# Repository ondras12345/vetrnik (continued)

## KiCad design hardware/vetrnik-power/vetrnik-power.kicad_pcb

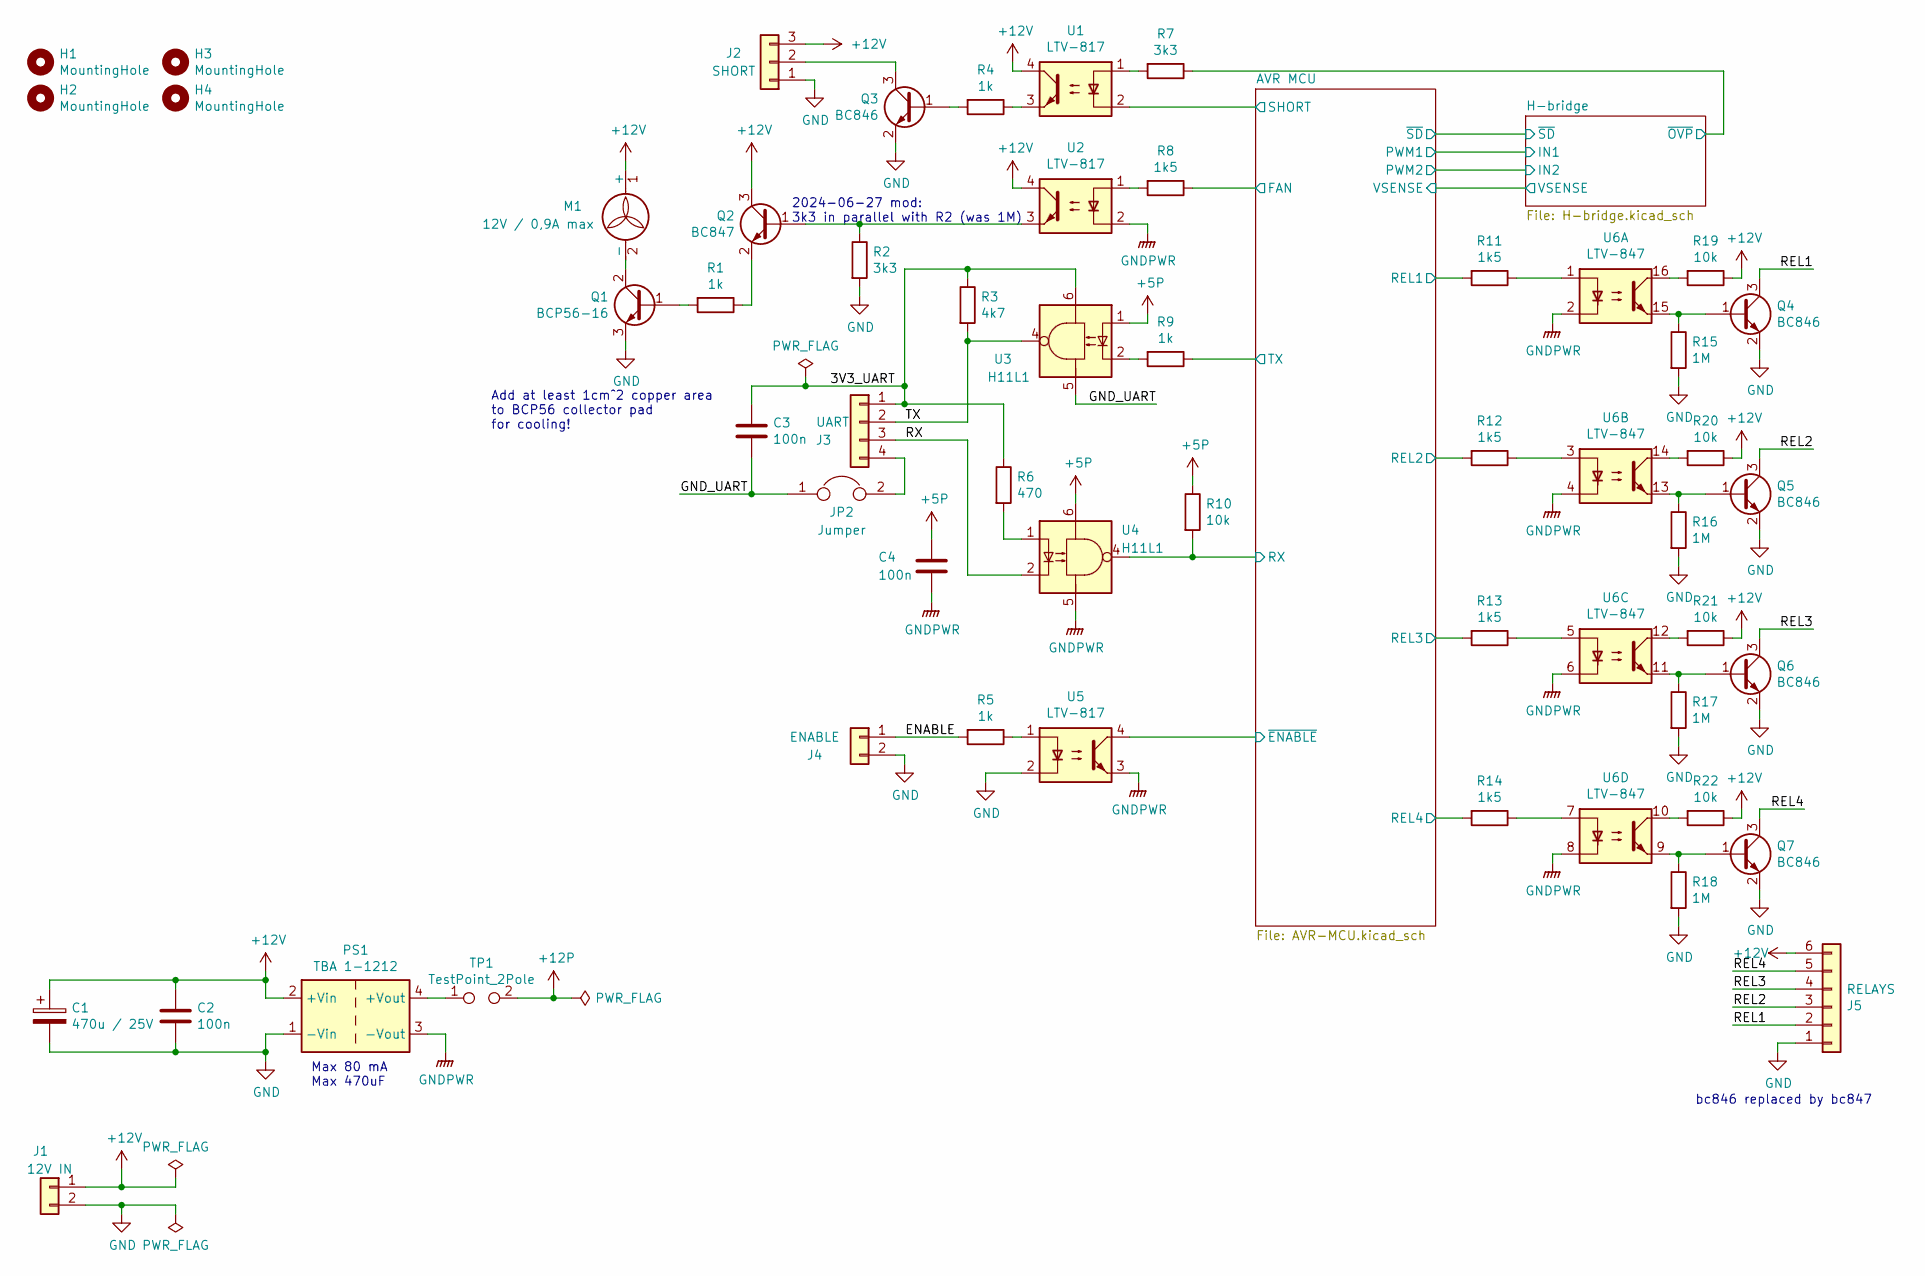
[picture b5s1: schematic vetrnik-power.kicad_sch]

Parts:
C1: 470u / 25V; CP_Radial_D10.0mm_P5.00mm
C2, C3, C4: 100n; C_1206_3216Metric_Pad1.33x1.80mm_HandSolder
H1, H2, H3, H4: MountingHole; MountingHole_3.2mm_M3
J1: 12V IN; Molex_KK-254_AE-6410-02A_1x02_P2.54mm_Vertical
J2: SHORT; Molex_KK-254_AE-6410-03A_1x03_P2.54mm_Vertical
J3: UART; Molex_KK-254_AE-6410-04A_1x04_P2.54mm_Vertical
J4: ENABLE; Molex_KK-254_AE-6410-02A_1x02_P2.54mm_Vertical
J5: RELAYS; Molex_KK-254_AE-6410-06A_1x06_P2.54mm_Vertical
JP2: Jumper; R_1206_3216Metric_Pad1.30x1.75mm_HandSolder
M1: 12V / 0,9A max; Molex_KK-254_AE-6410-02A_1x02_P2.54mm_Vertical
PS1: TBA 1-1212; Converter_DCDC_Murata_MEE1SxxxxSC_THT
Q1: BCP56-16; SOT-223-3_TabPin2
Q2: BC847; SOT-23
Q3, Q4, Q5, Q6, Q7: BC846; SOT-23
R1, R4, R5, R9: 1k; R_1206_3216Metric_Pad1.30x1.75mm_HandSolder
R2, R7: 3k3; R_1206_3216Metric_Pad1.30x1.75mm_HandSolder
R3: 4k7; R_1206_3216Metric_Pad1.30x1.75mm_HandSolder
R6: 470; R_1206_3216Metric_Pad1.30x1.75mm_HandSolder
R8, R11, R12, R13, R14: 1k5; R_1206_3216Metric_Pad1.30x1.75mm_HandSolder
R10, R19, R20, R21, R22: 10k; R_1206_3216Metric_Pad1.30x1.75mm_HandSolder
R15, R16, R17, R18: 1M; R_1206_3216Metric_Pad1.30x1.75mm_HandSolder
TP1: TestPoint_2Pole; PinHeader_1x02_P2.54mm_Vertical
U1, U2, U5: LTV-817; DIP-4_W7.62mm
U3, U4: H11L1; DIP-6_W7.62mm_LongPads
U6: LTV-847; DIP-16_W7.62mm

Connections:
+5P: C4.1, R10.1, U3.1, U4.6; also elsewhere on the board
+12P: TP1.2; also elsewhere on the board
+12V: C1.1, C2.1, J1.1, J2.3, J5.6, M1.1 (+), PS1.2 (+Vin), Q2.3 (C), R19.1, R20.1, R21.1, R22.1, U1.4, U2.4
/3V3_UART: C3.1, J3.1, R3.1, R6.1, U3.6
/AVR MCU/REL1: R11.2; also elsewhere on the board
/AVR MCU/REL2: R12.2; also elsewhere on the board
/AVR MCU/REL3: R13.2; also elsewhere on the board
/AVR MCU/REL4: R14.2; also elsewhere on the board
/AVR MCU/RX: R10.2, U4.4; also elsewhere on the board
/AVR MCU/SHORT: U1.2; also elsewhere on the board
/AVR MCU/TX: R9.1; also elsewhere on the board
/AVR MCU/~ENABLE: U5.4; also elsewhere on the board
/ENABLE: J4.1, R5.2
/GND_UART: C3.2, JP2.1, U3.5
/H-bridge/~OVP: R7.1; also elsewhere on the board
/REL1: J5.2, Q4.3 (C)
/REL2: J5.3, Q5.3 (C)
/REL3: J5.4, Q6.3 (C)
/REL4: J5.5, Q7.3 (C)
/RX: J3.3, U4.2
/TX: J3.2, R3.2, U3.4
GND: C1.2, C2.2, J1.2, J2.1, J4.2, J5.1, PS1.1 (-Vin), Q1.3 (E), Q3.2 (E), Q4.2 (E), Q5.2 (E), Q6.2 (E), Q7.2 (E), R2.2, R15.2, R16.2, R17.2, R18.2, U5.2
unnamed: J2.2, Q3.3 (C)
unnamed: J3.4, JP2.2
unnamed: M1.2 (-), Q1.2 (C), Q1.4 (C)
unnamed: PS1.4 (+Vout), TP1.1
unnamed: Q1.1 (B), R1.2
unnamed: Q2.1 (B), R2.1, U2.3
unnamed: Q2.2 (E), R1.1
unnamed: Q3.1 (B), R4.2
unnamed: Q4.1 (B), R15.1, U6.15
unnamed: Q5.1 (B), R16.1, U6.13
unnamed: Q6.1 (B), R17.1, U6.11
unnamed: Q7.1 (B), R18.1, U6.9
unnamed: R4.1, U1.3
unnamed: R5.1, U5.1
unnamed: R6.2, U4.1
unnamed: R7.2, U1.1
unnamed: R8.2, U2.1
unnamed: R9.2, U3.2
unnamed: R11.1, U6.1
unnamed: R12.1, U6.3
unnamed: R13.1, U6.5
unnamed: R14.1, U6.7
unnamed: R19.2, U6.16
unnamed: R20.2, U6.14
unnamed: R21.2, U6.12
unnamed: R22.2, U6.10

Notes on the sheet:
Add at least 1cm^2 copper area to BCP56 collector pad for cooling!
2024-06-27 mod: 3k3 in parallel with R2 (was 1M)
Max 80 mA Max 470uF
bc846 replaced by bc847

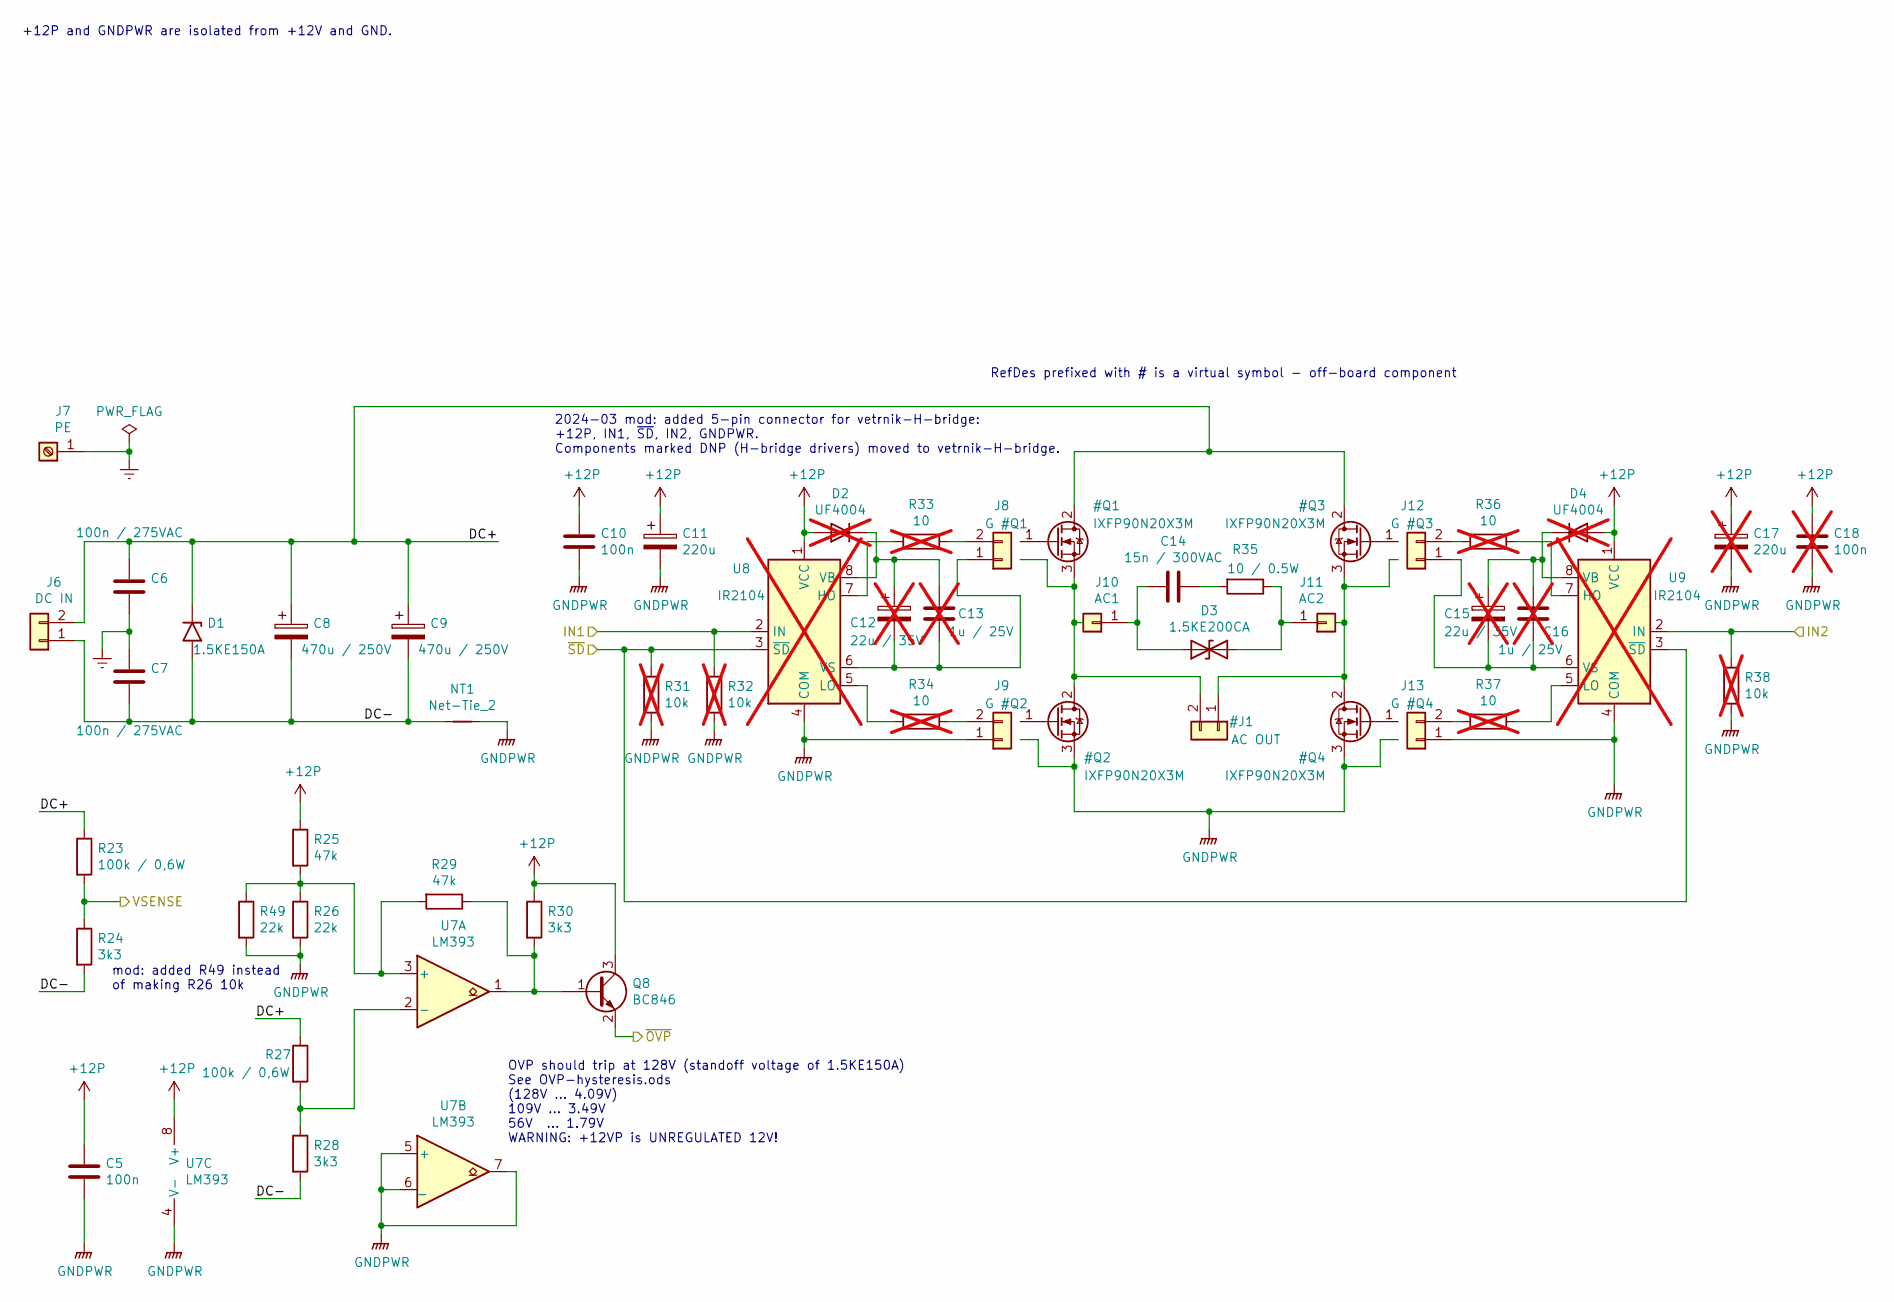
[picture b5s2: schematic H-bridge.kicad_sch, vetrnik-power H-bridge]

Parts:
C5, C10: 100n; C_1206_3216Metric_Pad1.33x1.80mm_HandSolder
C6, C7: 100n / 275VAC; C_Rect_L26.5mm_W10.5mm_P22.50mm_MKS4
C8, C9: 470u / 250V; CP_Radial_D30.0mm_P10.00mm_SnapIn
C11: 220u; CP_Radial_D8.0mm_P3.50mm
C12, C15: 22u / 35V; CP_Radial_D5.0mm_P2.00mm; not fitted
C13, C16: 1u / 25V; C_1206_3216Metric_Pad1.33x1.80mm_HandSolder; not fitted
C14: 15n / 300VAC; C_Rect_L18.0mm_W5.0mm_P15.00mm_FKS3_FKP3
C17: 220u; CP_Radial_D8.0mm_P3.50mm; not fitted
C18: 100n; C_1206_3216Metric_Pad1.33x1.80mm_HandSolder; not fitted
D1: 1.5KE150A; D_DO-201AE_P15.24mm_Horizontal
D2, D4: UF4004; D_DO-41_SOD81_P10.16mm_Horizontal; not fitted
D3: 1.5KE200CA; D_DO-201AE_P15.24mm_Horizontal
J6: DC IN; DG270-10.0-02P-14-00A
J7: PE; FS1536
J8: G #Q1; Molex_KK-254_AE-6410-02A_1x02_P2.54mm_Vertical
J9: G #Q2; Molex_KK-254_AE-6410-02A_1x02_P2.54mm_Vertical
J10: AC1; FS1536
J11: AC2; FS1536
J12: G #Q3; Molex_KK-254_AE-6410-02A_1x02_P2.54mm_Vertical
J13: G #Q4; Molex_KK-254_AE-6410-02A_1x02_P2.54mm_Vertical
NT1: Net-Tie_2; NetTie-2_SMD_Pad2.0mm
Q8: BC846; SOT-23
R23, R27: 100k / 0,6W; R_Axial_DIN0207_L6.3mm_D2.5mm_P10.16mm_Horizontal
R24, R28, R30: 3k3; R_1206_3216Metric_Pad1.30x1.75mm_HandSolder
R25, R29: 47k; R_1206_3216Metric_Pad1.30x1.75mm_HandSolder
R26, R49: 22k; R_1206_3216Metric_Pad1.30x1.75mm_HandSolder
R31, R32, R38: 10k; R_1206_3216Metric_Pad1.30x1.75mm_HandSolder; not fitted
R33, R34, R36, R37: 10; R_1206_3216Metric_Pad1.30x1.75mm_HandSolder; not fitted
R35: 10 / 0.5W; R_Axial_DIN0309_L9.0mm_D3.2mm_P12.70mm_Horizontal
U7: LM393; SOIC-8_3.9x4.9mm_P1.27mm
U8, U9: IR2104; SOIC-8_3.9x4.9mm_P1.27mm; not fitted

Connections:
+12P: C5.1, C10.1, C11.1, C17.1, C18.1, D2.2 (A), D4.2 (A), Q8.3 (C), R25.1, R30.1, U7.8 (V+), U8.1 (VCC), U9.1 (VCC); also elsewhere on the board
/AVR MCU/VSENSE: R23.2, R24.1; also elsewhere on the board
/AVR MCU/~SD: R31.1, U8.3 (~SD), U9.3 (~SD); also elsewhere on the board
/H-bridge/IN1: R32.1, U8.2 (IN); also elsewhere on the board
/H-bridge/IN2: R38.1, U9.2 (IN); also elsewhere on the board
/H-bridge/~OVP: Q8.2 (E); also elsewhere on the board
Earth: C6.2, C7.1, J7.1
unnamed: C12.1, C13.1, D2.1 (K), U8.8 (VB)
unnamed: C12.2, C13.2, J8.1, U8.6 (VS)
unnamed: C14.1, R35.2
unnamed: C14.2, D3.2 (A2), J10.1
unnamed: C15.1, C16.1, D4.1 (K), U9.8 (VB)
unnamed: C15.2, C16.2, J12.1, U9.6 (VS)
unnamed: D3.1 (A1), J11.1, R35.1
unnamed: J8.2, R33.1
unnamed: J9.2, R34.1
unnamed: J12.2, R36.2
unnamed: J13.2, R37.2
unnamed: Q8.1 (B), R29.1, R30.2, U7.1
unnamed: R25.2, R26.1, R29.2, R49.1, U7.3 (+)
unnamed: R27.2, R28.1, U7.2 (-)
unnamed: R33.2, U8.7 (HO)
unnamed: R34.2, U8.5 (LO)
unnamed: R36.1, U9.7 (HO)
unnamed: R37.1, U9.5 (LO)

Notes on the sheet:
2024-03 mod: added 5-pin connector for vetrnik-H-bridge: +12P, IN1, ~{SD}, IN2, GNDPWR. Components marked DNP (H-bridge drivers) moved to vetrnik-H-bridge.
+12P and GNDPWR are isolated from +12V and GND.
RefDes prefixed with # is a virtual symbol - off-board component
OVP should trip at 128V (standoff voltage of 1.5KE150A) See OVP-hysteresis.ods (128V ... 4.09V) 109V ... 3.49V 56V ... 1.79V WARNING: +12VP is UNREGULATED 12V!
mod: added R49 instead of making R26 10k

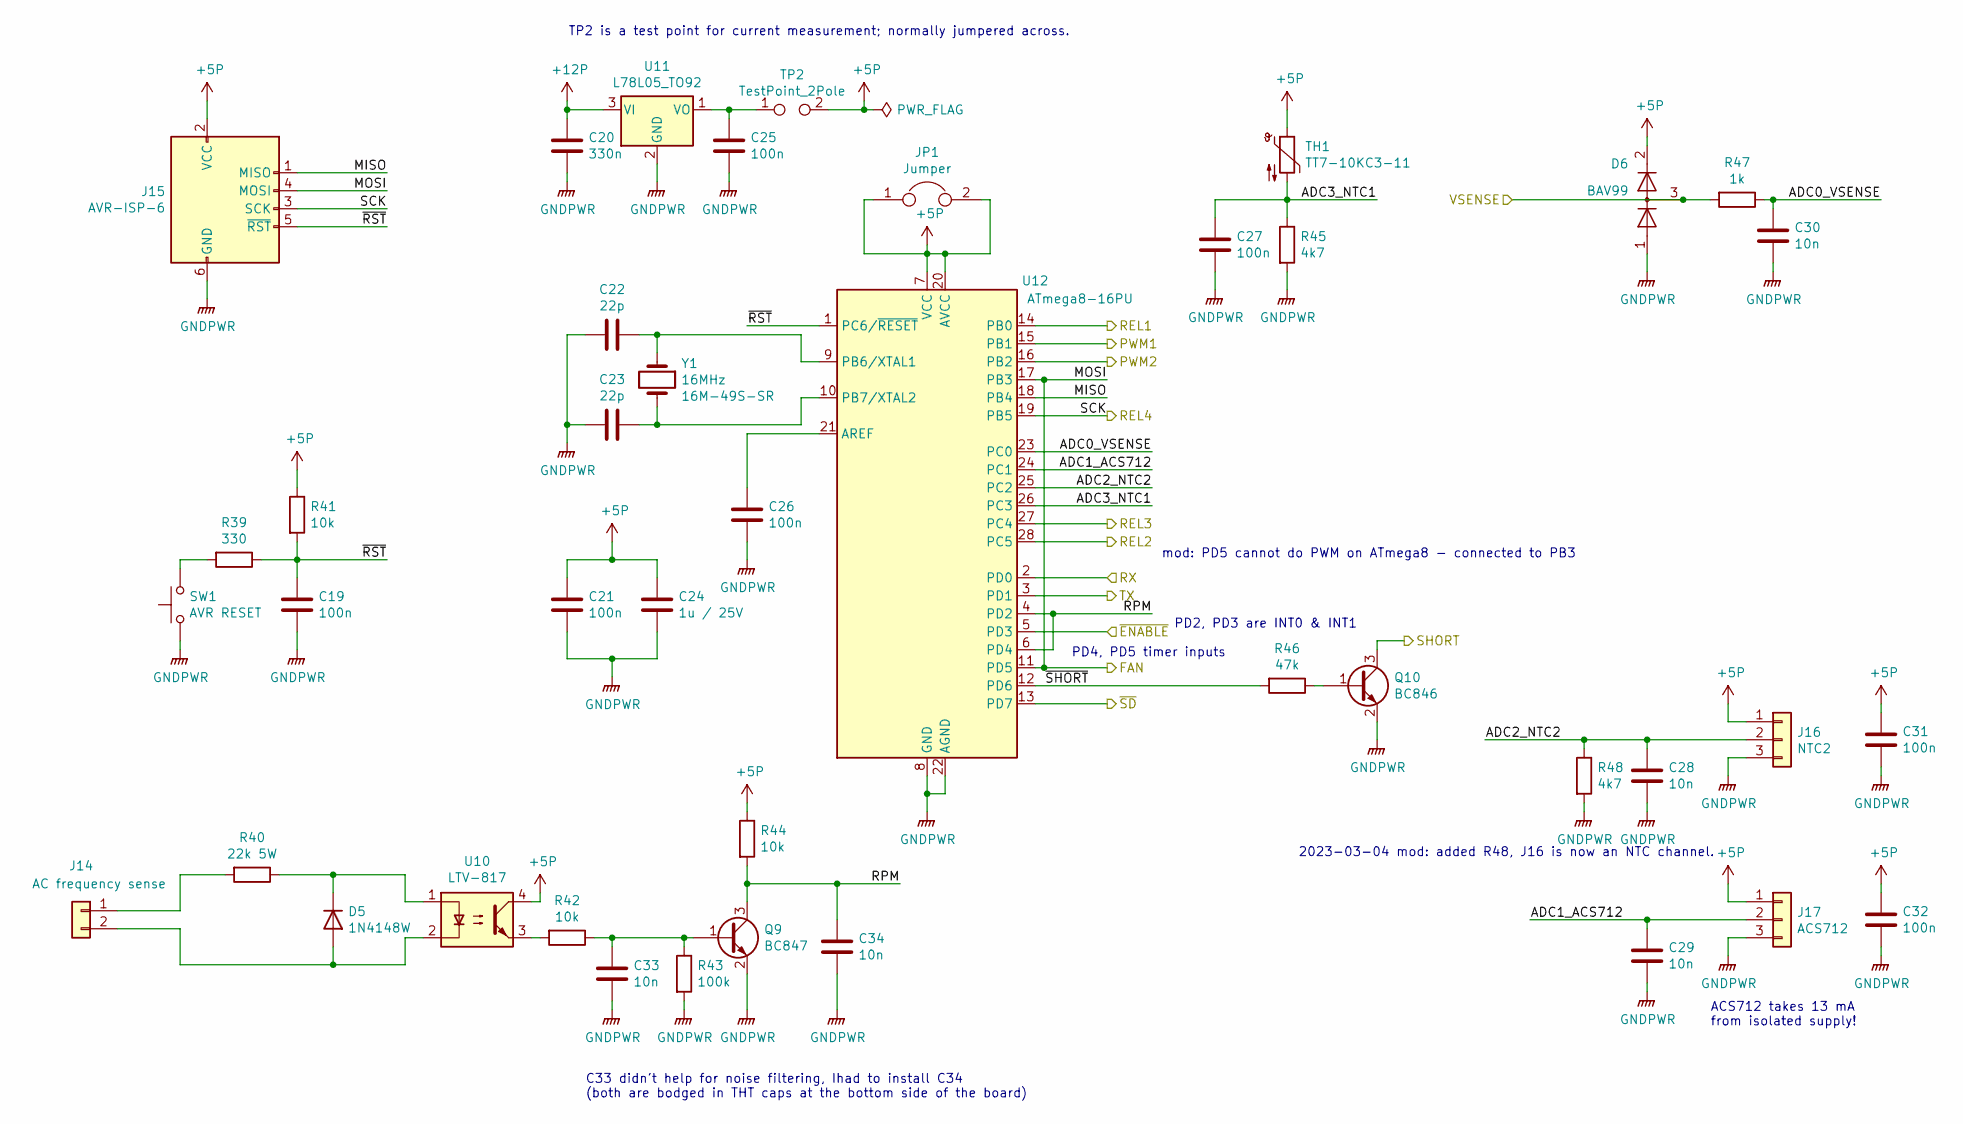
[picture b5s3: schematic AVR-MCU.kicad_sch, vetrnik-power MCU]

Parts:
C19, C21, C25, C26, C27, C31, C32: 100n; C_1206_3216Metric_Pad1.33x1.80mm_HandSolder
C20: 330n; C_1206_3216Metric_Pad1.33x1.80mm_HandSolder
C22, C23: 22p; C_1206_3216Metric_Pad1.33x1.80mm_HandSolder
C24: 1u / 25V; C_1206_3216Metric_Pad1.33x1.80mm_HandSolder
C28, C29, C30, C33, C34: 10n; C_1206_3216Metric_Pad1.33x1.80mm_HandSolder
D5: 1N4148W; D_SOD-123
D6: BAV99; SOT-23
J14: AC frequency sense; Molex_KK-254_AE-6410-02A_1x02_P2.54mm_Vertical
J15: AVR-ISP-6; IDC-Header_2x03_P2.54mm_Vertical
J16: NTC2; Molex_KK-254_AE-6410-03A_1x03_P2.54mm_Vertical
J17: ACS712; Molex_KK-254_AE-6410-03A_1x03_P2.54mm_Vertical
JP1: Jumper; R_1206_3216Metric_Pad1.30x1.75mm_HandSolder
Q9: BC847; SOT-23
Q10: BC846; SOT-23
R39: 330; R_1206_3216Metric_Pad1.30x1.75mm_HandSolder
R40: 22k 5W; R_Axial_DIN0922_L20.0mm_D9.0mm_P30.48mm_Horizontal
R41, R42, R44: 10k; R_1206_3216Metric_Pad1.30x1.75mm_HandSolder
R43: 100k; R_1206_3216Metric_Pad1.30x1.75mm_HandSolder
R45, R48: 4k7; R_1206_3216Metric_Pad1.30x1.75mm_HandSolder
R46: 47k; R_1206_3216Metric_Pad1.30x1.75mm_HandSolder
R47: 1k; R_1206_3216Metric_Pad1.30x1.75mm_HandSolder
SW1: AVR RESET; SW_PUSH_6mm_H4.3mm
TH1: TT7-10KC3-11; Molex_KK-254_AE-6410-02A_1x02_P2.54mm_Vertical
TP2: TestPoint_2Pole; PinHeader_1x02_P2.54mm_Vertical
U10: LTV-817; DIP-4_W7.62mm
U11: L78L05_TO92; TO-92L_HandSolder
U12: ATmega8-16PU; DIP-28_W7.62mm_Socket
Y1: 16MHz; Crystal_HC49-U_Vertical

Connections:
+5P: C21.1, C24.1, C31.1, C32.1, D6.2 (A), J15.2 (VCC), J16.1, J17.1, JP1.1, JP1.2, R41.1, R44.1, TH1.1, TP2.2, U10.4, U12.7 (VCC), U12.20 (AVCC); also elsewhere on the board
+12P: C20.1, U11.3 (VI); also elsewhere on the board
/AVR MCU/ADC0_VSENSE: C30.1, R47.1, U12.23 (PC0)
/AVR MCU/ADC1_ACS712: C29.1, J17.2, U12.24 (PC1)
/AVR MCU/ADC2_ACS712_2: C28.1, J16.2, R48.1, U12.25 (PC2)
/AVR MCU/ADC3_NTC1: C27.1, R45.1, TH1.2, U12.26 (PC3)
/AVR MCU/MISO: J15.1 (MISO), U12.18 (PB4)
/AVR MCU/REL1: U12.14 (PB0); also elsewhere on the board
/AVR MCU/REL2: U12.28 (PC5); also elsewhere on the board
/AVR MCU/REL3: U12.27 (PC4); also elsewhere on the board
/AVR MCU/REL4: J15.3 (SCK), U12.19 (PB5); also elsewhere on the board
/AVR MCU/RPM: C34.1, Q9.3 (C), R44.2, U12.4 (PD2), U12.6 (PD4)
/AVR MCU/RX: U12.2 (PD0); also elsewhere on the board
/AVR MCU/SHORT: Q10.3 (C); also elsewhere on the board
/AVR MCU/TX: U12.3 (PD1); also elsewhere on the board
/AVR MCU/VSENSE: D6.3 (K), R47.2; also elsewhere on the board
/AVR MCU/~ENABLE: U12.5 (PD3); also elsewhere on the board
/AVR MCU/~RST: C19.1, J15.5 (~RST), R39.1, R41.2, U12.1 (PC6/~RESET)
/AVR MCU/~SD: U12.13 (PD7); also elsewhere on the board
/AVR MCU/~SHORT: R46.2, U12.12 (PD6)
/H-bridge/IN1: U12.15 (PB1); also elsewhere on the board
/H-bridge/IN2: U12.16 (PB2); also elsewhere on the board
unnamed: C22.1, U12.9 (PB6/XTAL1), Y1.1
unnamed: C23.1, U12.10 (PB7/XTAL2), Y1.2
unnamed: C25.1, TP2.1, U11.1 (VO)
unnamed: C26.1, U12.21 (AREF)
unnamed: D5.1 (K), R40.1, U10.1
unnamed: D5.2 (A), J14.2, U10.2
unnamed: J14.1, R40.2
unnamed: C33.1, Q9.1 (B), R42.1, R43.1
unnamed: Q10.1 (B), R46.1
unnamed: R39.2, SW1.2
unnamed: R42.2, U10.3

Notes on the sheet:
mod: PD5 cannot do PWM on ATmega8 - connected to PB3
C33 didn't help for noise filtering, Ihad to install C34 (both are bodged in THT caps at the bottom side of the board)
TP2 is a test point for current measurement; normally jumpered across.
PD2, PD3 are INT0 & INT1
PD4, PD5 timer inputs
2023-03-04 mod: added R48, J16 is now an NTC channel.
ACS712 takes 13 mA from isolated supply!

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
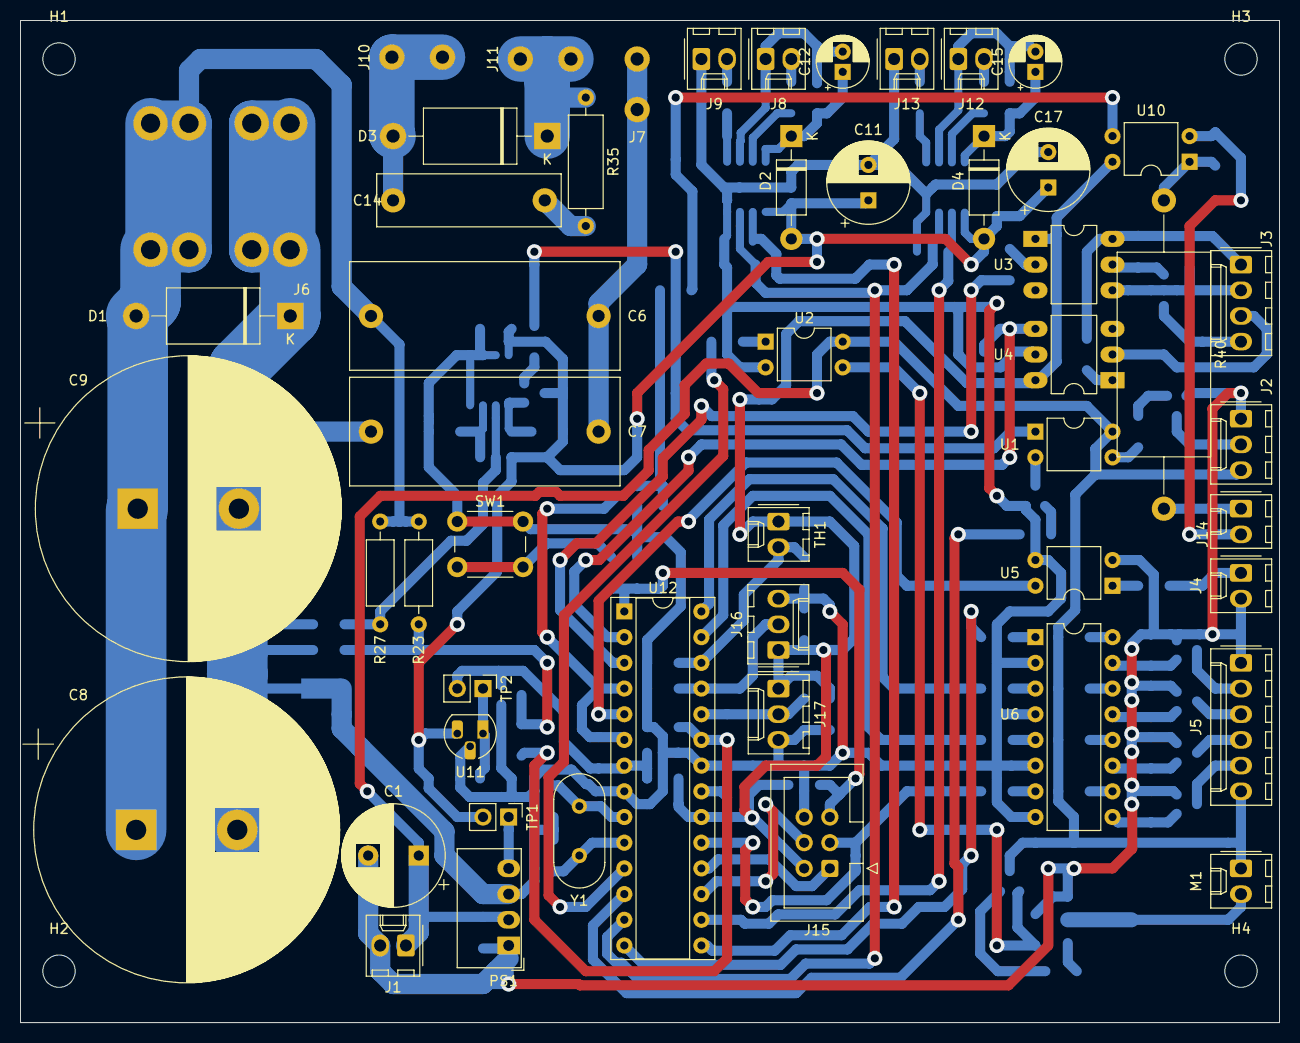
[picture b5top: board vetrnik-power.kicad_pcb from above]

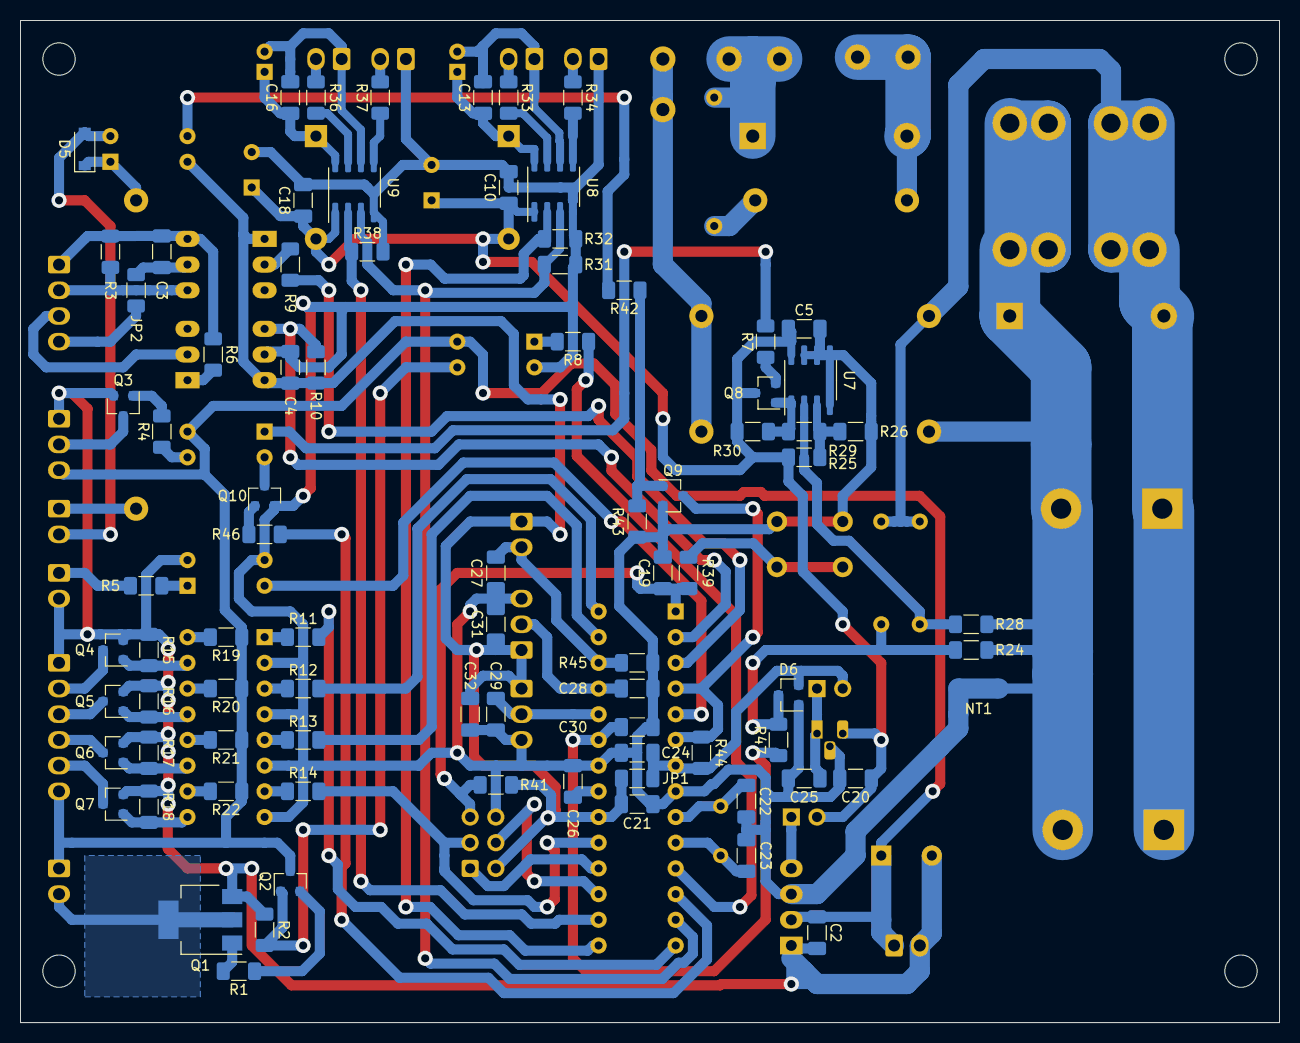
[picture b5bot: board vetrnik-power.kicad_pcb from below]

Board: 2 copper layers, 124.5 x 99.1 mm, 138 parts (83 on the bottom side), 95 nets.

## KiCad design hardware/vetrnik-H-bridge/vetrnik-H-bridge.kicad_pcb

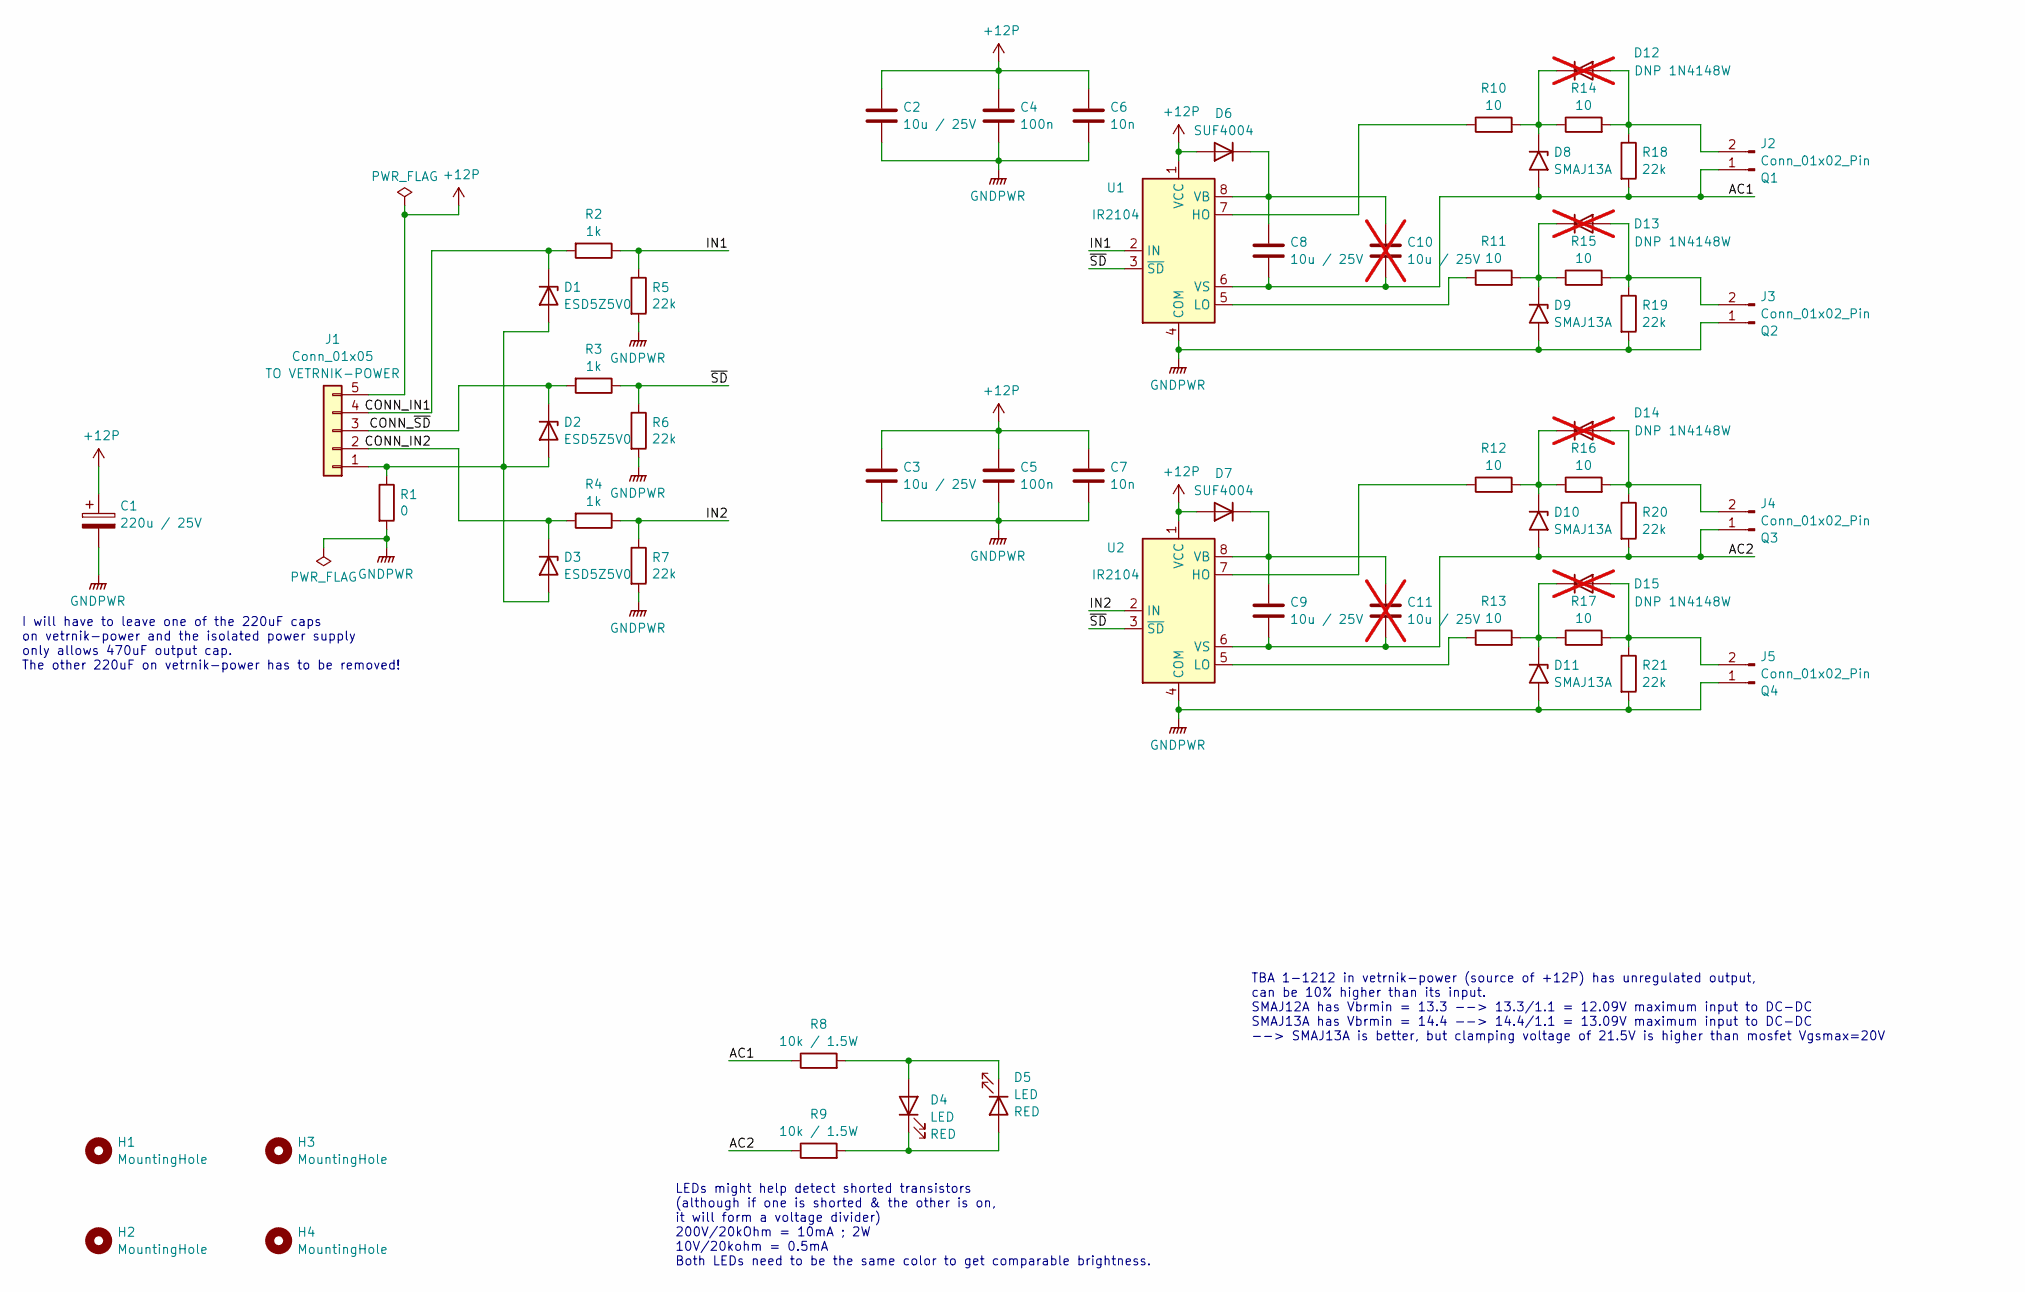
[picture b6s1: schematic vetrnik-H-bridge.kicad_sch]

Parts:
C1: 220u / 25V; CP_Elec_8x10
C2, C3, C8, C9: 10u / 25V; C_1206_3216Metric_Pad1.33x1.80mm_HandSolder
C4, C5: 100n; C_1206_3216Metric_Pad1.33x1.80mm_HandSolder
C6, C7: 10n; C_1206_3216Metric_Pad1.33x1.80mm_HandSolder
C10, C11: 10u / 25V; C_1206_3216Metric_Pad1.33x1.80mm_HandSolder; not fitted
D1, D2, D3: ESD5Z5V0; D_SOD-523
D4, D5: LED; LED_1206_3216Metric_Pad1.42x1.75mm_HandSolder
D6, D7: SUF4004; D_MELF_Handsoldering
D8, D9, D10, D11: SMAJ13A; D_SMA
D12, D13, D14, D15: DNP 1N4148W; D_SOD-123; not fitted
H1, H2, H3, H4: MountingHole; MountingHole_3.2mm_M3
J1: Conn_01x05; SolderWire-0.25sqmm_1x05_P4.2mm_D0.65mm_OD1.7mm_Relief
J2, J3, J4, J5: Conn_01x02_Pin; SolderWire-0.15sqmm_1x02_P4mm_D0.5mm_OD1.5mm_Relief
R1: 0; R_1206_3216Metric_Pad1.30x1.75mm_HandSolder
R2, R3, R4: 1k; R_1206_3216Metric_Pad1.30x1.75mm_HandSolder
R5, R6, R7, R18, R19, R20, R21: 22k; R_1206_3216Metric_Pad1.30x1.75mm_HandSolder
R8, R9: 10k / 1.5W; R_2512_6332Metric_Pad1.40x3.35mm_HandSolder
R10, R11, R12, R13, R14, R15, R16, R17: 10; R_1206_3216Metric_Pad1.30x1.75mm_HandSolder
U1, U2: IR2104; SOIC-8_3.9x4.9mm_P1.27mm

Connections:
+12P: C1.1, C2.1, C3.1, C4.1, C5.1, C6.1, C7.1, D6.2 (A), D7.2 (A), J1.5, U1.1 (VCC), U2.1 (VCC)
/AC1: C8.2, C10.2, D8.2 (A2), J2.1, R8.1, R18.2, U1.6 (VS)
/AC2: C9.2, C11.2, D10.2 (A2), J4.1, R9.1, R20.2, U2.6 (VS)
/CONN_IN1: D1.1 (K), J1.4, R2.2
/CONN_IN2: D3.1 (K), J1.2, R4.2
/CONN_~SD: D2.1 (K), J1.3, R3.2
/IN1: R2.1, R5.1, U1.2 (IN)
/IN2: R4.1, R7.1, U2.2 (IN)
/~SD: R3.1, R6.1, U1.3 (~SD), U2.3 (~SD)
GNDPWR: C1.2, C2.2, C3.2, C4.2, C5.2, C6.2, C7.2, D9.2 (A2), D11.2 (A2), J3.1, J5.1, R1.2, R5.2, R6.2, R7.2, R19.2, R21.2, U1.4 (COM), U2.4 (COM)
unnamed: D1.2 (A), D2.2 (A), D3.2 (A), J1.1, R1.1
unnamed: D4.2 (A), D5.1 (K), R8.2
unnamed: D4.1 (K), D5.2 (A), R9.2
unnamed: C8.1, C10.1, D6.1 (K), U1.8 (VB)
unnamed: C9.1, C11.1, D7.1 (K), U2.8 (VB)
unnamed: D10.1 (A1), D14.1 (K), R12.2, R16.1
unnamed: D11.1 (A1), D15.1 (K), R13.2, R17.1
unnamed: D12.2 (A), J2.2, R14.2, R18.1
unnamed: D8.1 (A1), D12.1 (K), R10.2, R14.1
unnamed: D13.2 (A), J3.2, R15.2, R19.1
unnamed: D9.1 (A1), D13.1 (K), R11.2, R15.1
unnamed: D14.2 (A), J4.2, R16.2, R20.1
unnamed: D15.2 (A), J5.2, R17.2, R21.1
unnamed: R10.1, U1.7 (HO)
unnamed: R11.1, U1.5 (LO)
unnamed: R12.1, U2.7 (HO)
unnamed: R13.1, U2.5 (LO)

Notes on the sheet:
LEDs might help detect shorted transistors (although if one is shorted & the other is on, it will form a voltage divider) 200V/20kOhm = 10mA ; 2W 10V/20kohm = 0.5mA Both LEDs need to be the same color to get comparable brightness.
I will have to leave one of the 220uF caps on vetrnik-power and the isolated power supply only allows 470uF output cap. The other 220uF on vetrnik-power has to be removed!
TBA 1-1212 in vetrnik-power (source of +12P) has unregulated output, can be 10% higher than its input. SMAJ12A has Vbrmin = 13.3 --> 13.3/1.1 = 12.09V maximum input to DC-DC SMAJ13A has Vbrmin = 14.4 --> 14.4/1.1 = 13.09V maximum input to DC-DC --> SMAJ13A is better, but clamping voltage of 21.5V i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

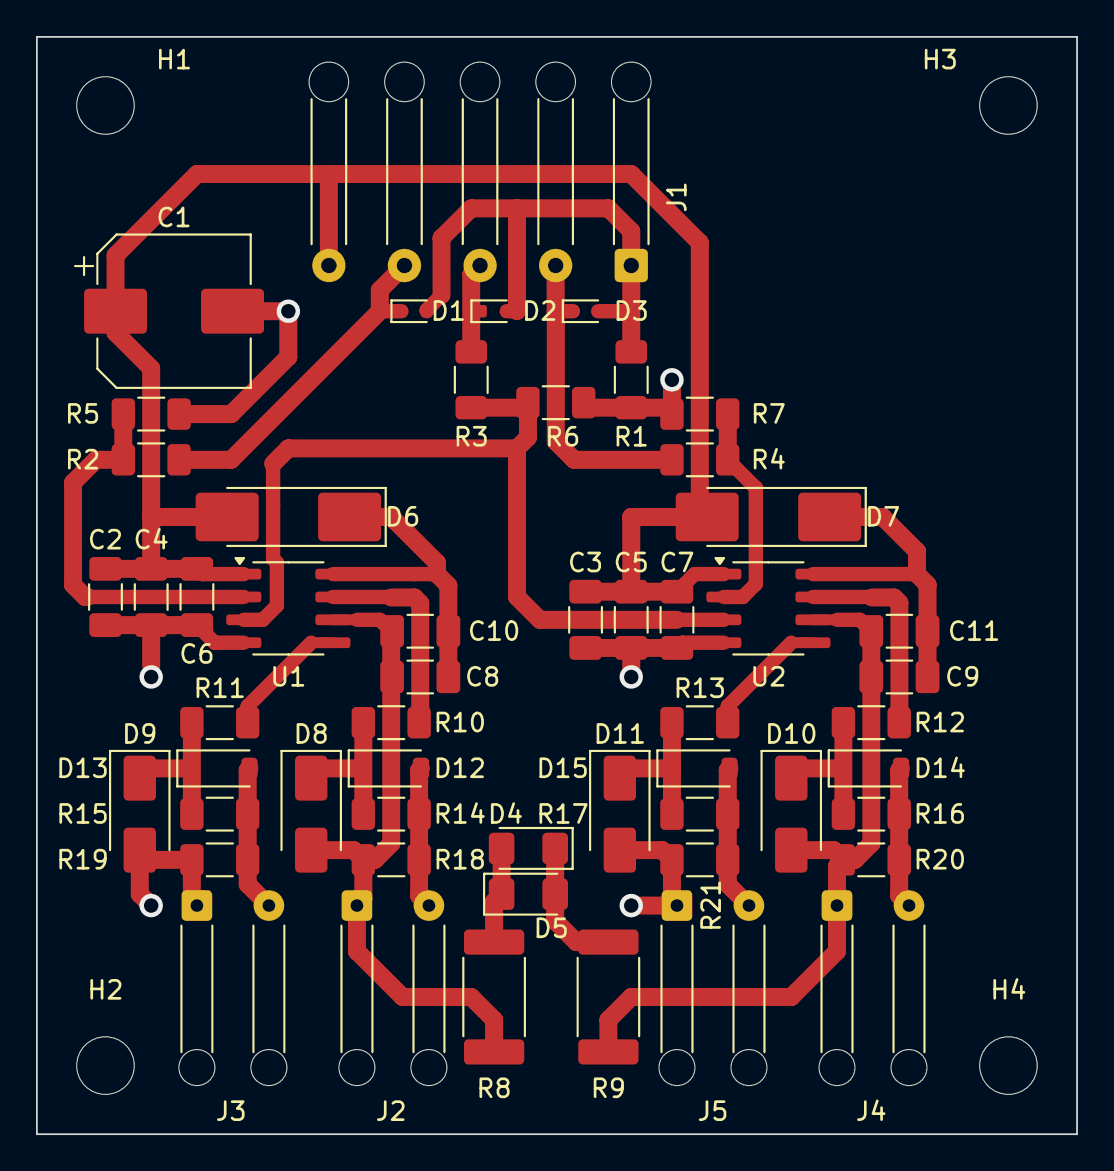
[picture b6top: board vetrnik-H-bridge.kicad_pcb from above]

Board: 2 copper layers, 57.8 x 61.0 mm, 58 parts (0 on the bottom side), 27 nets.
